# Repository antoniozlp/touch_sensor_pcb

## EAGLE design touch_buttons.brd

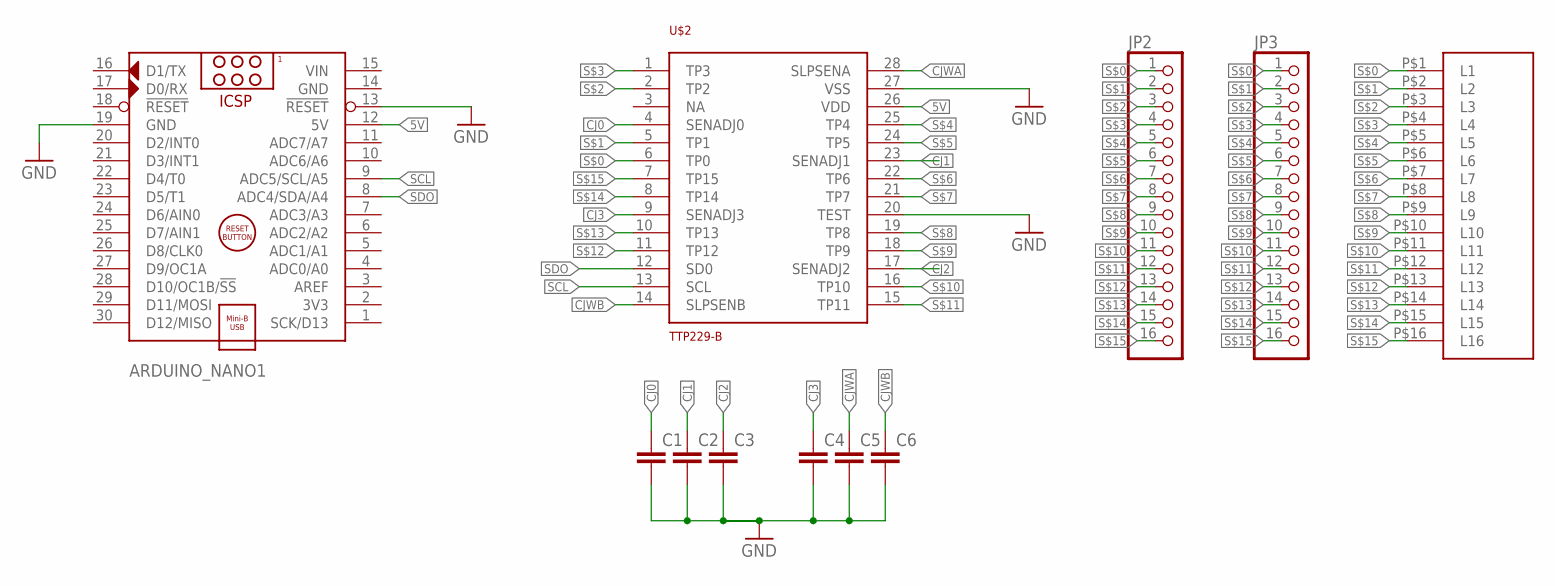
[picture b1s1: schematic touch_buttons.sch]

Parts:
ARDUINO_NANO1: ARDUINO_NANO
C1, C2, C3, C4, C5, C6: 1UF-25V-10%(0805)"; 0805-CAP
JP2, JP3: PINHD-1X16; 1X16
U$2: TTP229-B; SSOP28
U$3: SLIDE_TOUCH_RAR_V1; SLIDE_TOUCH_BAR_V1

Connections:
5V: ARDUINO_NANO1.12 (5V), U$2.26 (VDD)
CJ0: C1.1, U$2.4 (SENADJ0)
CJ1: C2.1, U$2.23 (SENADJ1)
CJ2: C3.1, U$2.17 (SENADJ2)
CJ3: C4.1, U$2.9 (SENADJ3)
CJWA: C5.1, U$2.28 (SLPSENA)
CJWB: C6.1, U$2.14 (SLPSENB)
GND: ARDUINO_NANO1.13 (!RESET), ARDUINO_NANO1.14 (GND), ARDUINO_NANO1.19 (GND), C1.2, C2.2, C3.2, C4.2, C5.2, C6.2, U$2.20 (TEST), U$2.27 (VSS)
S$0: JP2.1, JP3.1, U$2.6 (TP0), U$3.P$1 (L1)
S$1: JP2.2, JP3.2, U$2.5 (TP1), U$3.P$2 (L2)
S$2: JP2.3, JP3.3, U$2.2 (TP2), U$3.P$3 (L3)
S$3: JP2.4, JP3.4, U$2.1 (TP3), U$3.P$4 (L4)
S$4: JP2.5, JP3.5, U$2.25 (TP4), U$3.P$5 (L5)
S$5: JP2.6, JP3.6, U$2.24 (TP5), U$3.P$6 (L6)
S$6: JP2.7, JP3.7, U$2.22 (TP6), U$3.P$7 (L7)
S$7: JP2.8, JP3.8, U$2.21 (TP7), U$3.P$8 (L8)
S$8: JP2.9, JP3.9, U$2.19 (TP8), U$3.P$9 (L9)
S$9: JP2.10, JP3.10, U$2.18 (TP9), U$3.P$10 (L10)
S$10: JP2.11, JP3.11, U$2.16 (TP10), U$3.P$11 (L11)
S$11: JP2.12, JP3.12, U$2.15 (TP11), U$3.P$12 (L12)
S$12: JP2.13, JP3.13, U$2.11 (TP12), U$3.P$13 (L13)
S$13: JP2.14, JP3.14, U$2.10 (TP13), U$3.P$14 (L14)
S$14: JP2.15, JP3.15, U$2.8 (TP14), U$3.P$15 (L15)
S$15: JP2.16, JP3.16, U$2.7 (TP15), U$3.P$16 (L16)
SCL: ARDUINO_NANO1.9 (ADC5/SCL/A5), U$2.13 (SCL)
SDO: ARDUINO_NANO1.8 (ADC4/SDA/A4), U$2.12 (SD0)
VIN: ARDUINO_NANO1.15 (VIN)

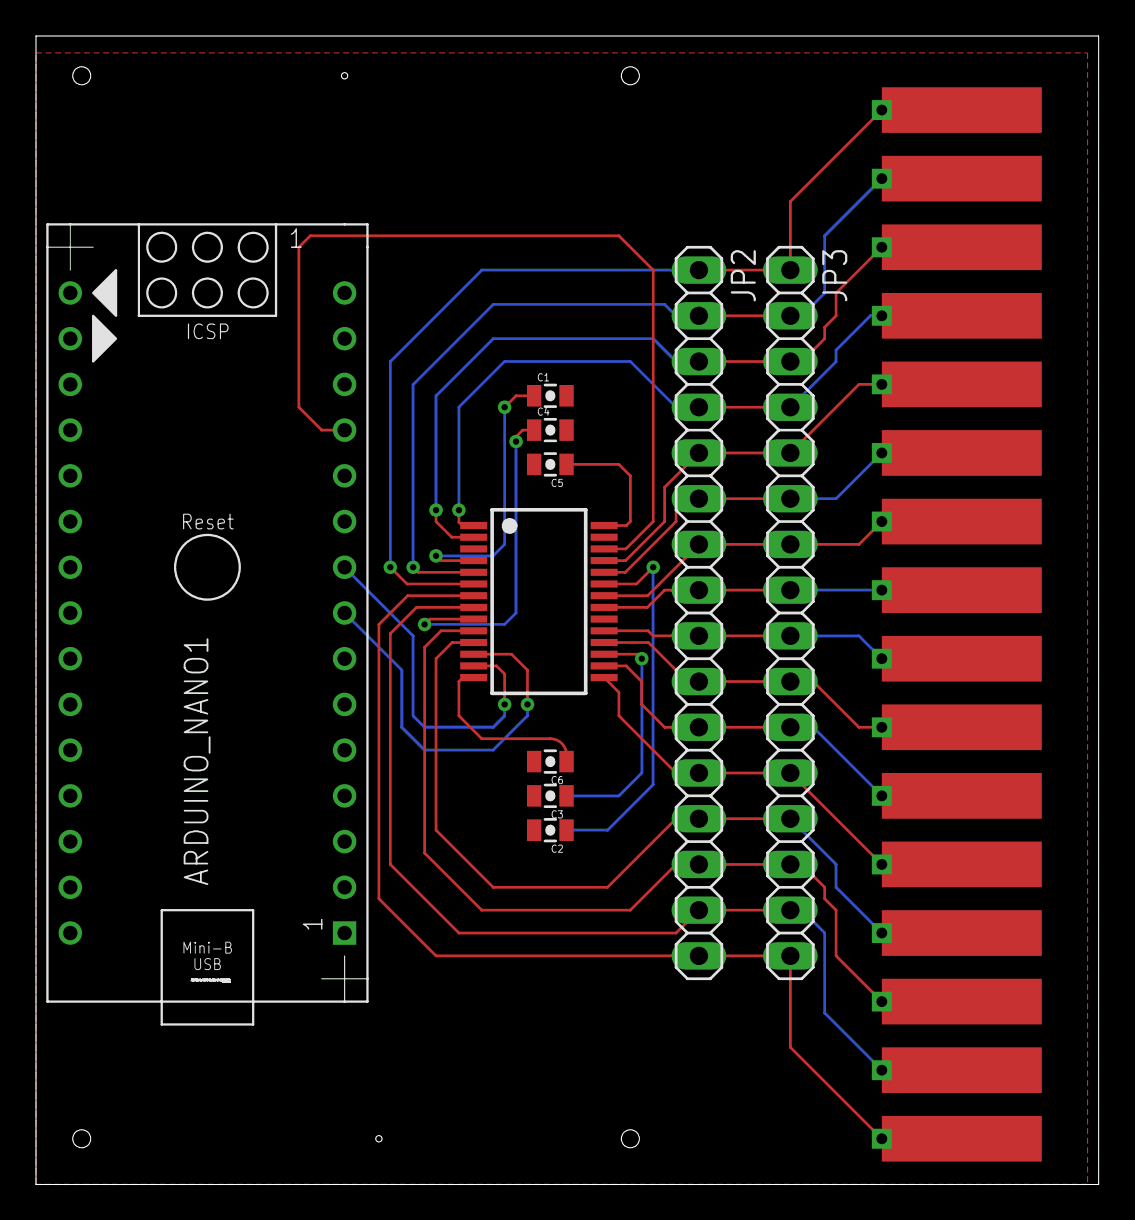
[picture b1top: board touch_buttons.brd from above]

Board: 2 copper layers, 59.0 x 63.8 mm, 11 parts (0 on the bottom side), 26 nets.

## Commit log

2018-11-24 add gitignore file

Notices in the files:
parts and their libraries:
SparkFun-Capacitors: Licensing: Creative Commons ShareAlike 4.0 International - https://creativecommons.org/licenses/by-sa/4.0
SparkFun: Licensing: CC v3.0 Share-Alike You are welcome to use this library for commercial purposes.
